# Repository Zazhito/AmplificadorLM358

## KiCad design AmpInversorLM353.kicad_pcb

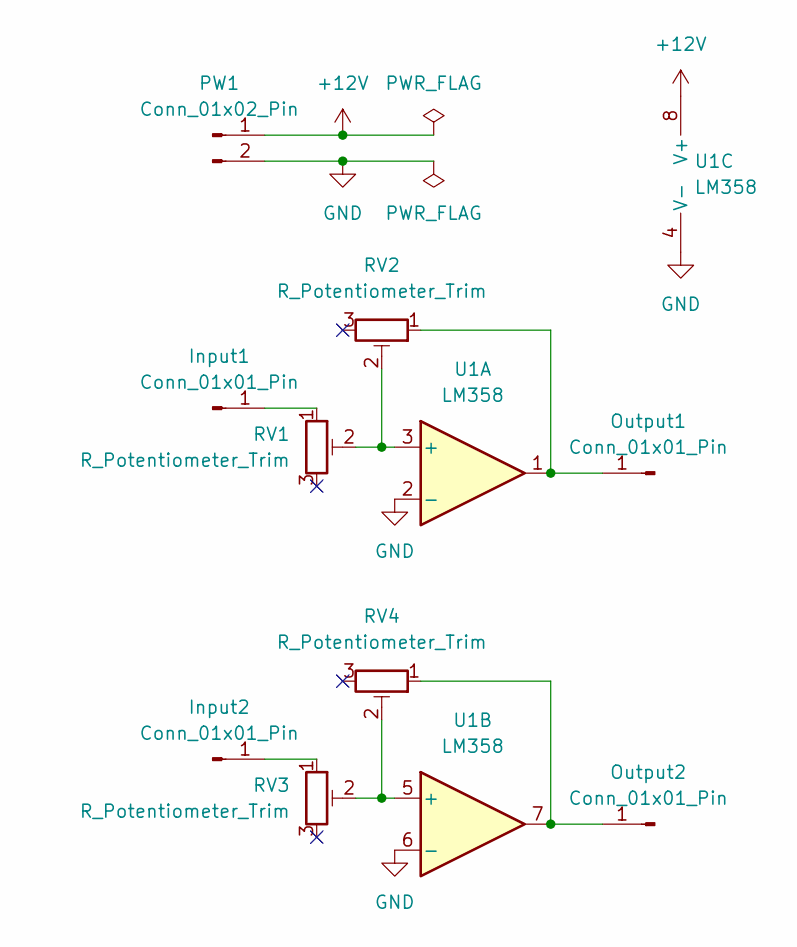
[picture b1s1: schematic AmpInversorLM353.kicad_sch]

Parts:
Input1, Input2: Conn_01x01_Pin; PinHeader_1x01_P2.54mm_Vertical
Output1, Output2: Conn_01x01_Pin; PinHeader_1x01_P2.54mm_Vertical
PW1: Conn_01x02_Pin; JST_EH_B2B-EH-A_1x02_P2.50mm_Vertical
RV1, RV2, RV3, RV4: R_Potentiometer_Trim; Potentiometer_Bourns_3296W_Vertical
U1: LM358; DIP-8_W7.62mm

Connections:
+12V: PW1.1, U1.8 (V+)
GND: PW1.2, U1.2 (-), U1.4 (V-), U1.6 (-)
unnamed: Input1.1, RV1.1
unnamed: Input2.1, RV3.1
unnamed: Output1.1, RV2.1, U1.1
unnamed: Output2.1, RV4.1, U1.7
unnamed: RV1.2, RV2.2, U1.3 (+)
unnamed: RV3.2, RV4.2, U1.5 (+)

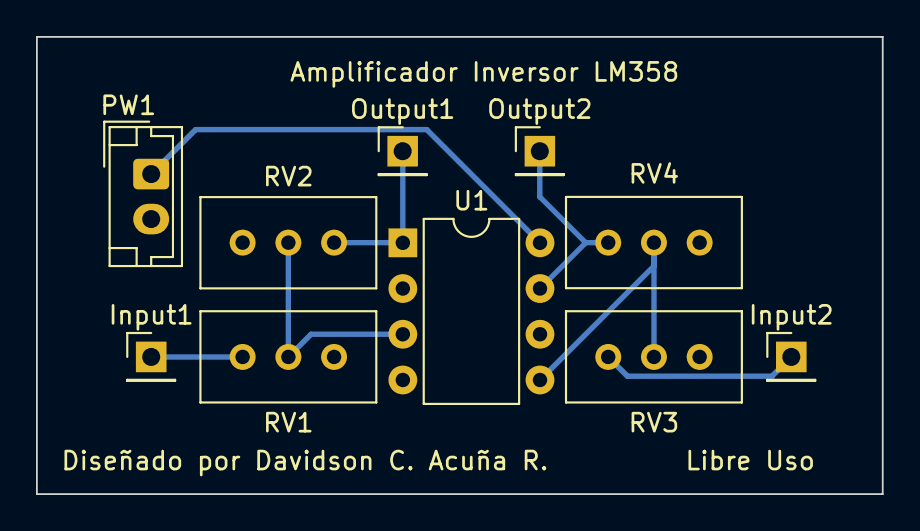
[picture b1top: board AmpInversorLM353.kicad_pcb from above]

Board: 2 copper layers, 47.0 x 25.4 mm, 10 parts (0 on the bottom side), 8 nets.

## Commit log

2024-04-02 Add files via upload
    Vo1 = -(RV2/RV1)*Vi1
    Vo2 = -(RV4/RV3)*Vi2
